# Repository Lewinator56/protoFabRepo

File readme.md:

# Prototyping and Fabrication Repo!

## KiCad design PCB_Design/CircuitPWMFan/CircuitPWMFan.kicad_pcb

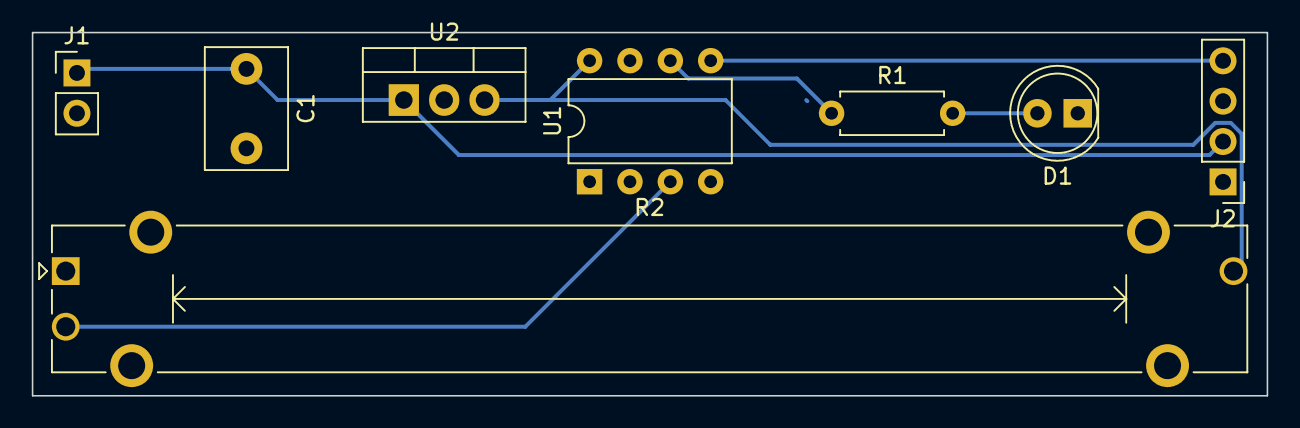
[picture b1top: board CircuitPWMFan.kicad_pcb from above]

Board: 2 copper layers, 77.7 x 22.9 mm, 8 parts (0 on the bottom side), 7 nets.

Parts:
C1: 0.33uF; C_Disc_D7.5mm_W5.0mm_P5.00mm
D1: LED; LED_D5.0mm
J1: Conn_01x02_Male; PinHeader_1x02_P2.54mm_Vertical
J2: Conn_01x04_Male; PinHeader_1x04_P2.54mm_Vertical
R1: 110; R_Axial_DIN0207_L6.3mm_D2.5mm_P7.62mm_Horizontal
R2: PTA6043-2015DP-B103; Potentiometer_Bourns_PTA6043_Single_Slide
U1: ATtiny85-20P; DIP-8_W7.62mm
U2: LM7805_TO220; TO-220-3_Vertical

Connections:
5V: R2.3, U1.8 (VCC), U2.3 (VO)
12V: C1.1, J1.1, J2.2, U2.1 (VI)
ADC2: R2.2, U1.3 (XTAL2/PB4)
GND: C1.2, D1.1 (K), J1.2, J2.1, R2.1, U1.4 (GND), U2.2 (GND)
LED: R1.1, U1.6 (PB1)
unnamed: D1.2 (A), R1.2
PWM: J2.4, U1.5 (AREF/PB0)

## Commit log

2022-04-03 Added enclosure CAD Files and Pictures
2022-04-03 move cad to separate folder
2022-04-03 Organised files into folders
2022-04-03 fixed missing folder
2022-04-07 images of work produced in workshop
    pictures and videos taken from workshops. from original idea to packaging creation
2022-04-13 Added PCB Design Files
2022-04-13 Updated Enclosure CAD Files
2022-05-02 PCB printing
    Images from attempting to print the circuit board (no working end product)
2022-05-20 Image Consolidation
    Sorted the file system so all images are in one place, plus some additional images
2022-05-20 images
    All images I have, plus the code file
2022-05-20 marketing
    meh
